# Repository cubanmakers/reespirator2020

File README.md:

# Reespirator 2020

Este repositorio pretende documentar y organizar los pasos para fabricar prototipos de  **Reespirator-2020**, un respirador open-source basado en el sistema de ventilación mecánica Jackson-Rees, diseñado y mejorado a partir de los prototipos elaborados por el equipo de Reesistencia Team para todas aquellas personas, organizaciones o empresas que quieran fabricarlo en cualquier parte del mundo.  

> ESTA DOCUMENTACIÓN ESTÁ EN ELABORACIÓN, COMPRUEBE REGULARMENTE LOS CAMBIOS, LAS PRIMERAS VERSIONES PUBLICADAS ESTÁN DESACTUALIZADAS. 

## Disclaimer
*Recuerde que un respirador es un dispositivo médico que sólo puede ser utilizado por personal cualificado y que un mal respirador o un respirador mal utilizado puede matar.*

La presente documentación **NO PERMITE CONSTRUIR UN RESPIRADOR FINAL**, sólo se publica para que se pueda fabricar PROTOTIPOS para investigación. 

## Info
*¿Qué es Reespirator 2020?*

El dispositivo Reespirator 2020 es un prototipo de sistema respirador de emergencia con elementos disponibles por la mayoría de las personas en cualquier parte del mundo, de rápida construcción y con la capacidad para mantener constantes ventilatorias aceptables en un paciente afecto de [Síndrome de Distrés Respiratorio Agudo](https://es.wikipedia.org/wiki/S%C3%ADndrome_de_dificultad_respiratoria_aguda) o SDRA.

Aunque el origen de Reespirator es España, debido a las regulaciones y validaciones necesarias para los productos médicos, y aunque Reespirator 23 de Reesistencia Team en el que se ha basado este nuevo diseño, ha superado varias pruebas preclínicas con animales, y de compatibilidad electromagnética, suponemos que este dispositivo nunca se llegará a fabricar masivamente en España, dónde afortunadamente lo peor de la crisis del COVID-19 parece que ya ha pasado (08/04/20); esperamos que este y otros diseños puedan ser útiles en otros países.

Aún así no nos damos por vencidos y seguiremos desarrollando el proyecto al menos en 2 versiones:

* Versión low cost (basada en Arduino y con caja de metacrilato, madera...)
* Versión pro (con un autómata PLC + un HMI y caja de chapa plegada en acero inoxidable)

## Primeros pasos
Antes de montar un respirador lea toda la documentación posible e infórmese bien, si necesitas alguna aclaración abra un Issue y lo corregiremos en cuanto podamos. Si crees que puedes mejorar el diseño o el código envíanos un Pull request.

## [Estructura básica](https://gitlab.com/reespirator/reespirator-doc/-/blob/master/CASE.md)
Reespirator 2020 consta de una [caja](https://gitlab.com/reespirator/reespirator-doc/-/blob/master/CASE.md) diseñada para fabricarse mediante corte láser que contiene casi todos elementos del respirador en su interior. En el prototipo actual las piezas del prototipo se han diseñado para su corte por láser en metacrilato si bien la imagen anterior corresponde a la nueva evolución que podrá fabricarse también con chapa plegada.

## [Sistema neumático](https://gitlab.com/reespirator/reespirator-doc/-/blob/master/NEUMATIC.md)
El [sistema neumático](https://gitlab.com/reespirator/reespirator-doc/-/blob/master/NEUMATIC.md) del Reespirator 2020 está basado en un sistema Jackson-Rees. Reespirator 2020 utiliza además una serie de válvulas, sensores de presión y caudal y tubuladuras para hacer llegar al aire a los pulmones del paciente.

## [Mecánica](https://gitlab.com/reespirator/reespirator-doc/-/blob/master/MECHANIC.md)
El [sistema mecánico](https://gitlab.com/reespirator/reespirator-doc/-/blob/master/MECHANIC.md) pretende realizar los movimientos necesarios para realizar las maniobras de inspiración y espiración forzada del paciente mediante elementos mecánicos sustituyendo al personal humano que utilizaría el sistema de ventilación.

## [Electrónica](https://gitlab.com/reespirator/reespirator-doc/-/blob/master/ELECTRONICS.md)
La [electrónica](https://gitlab.com/reespirator/reespirator-doc/-/blob/master/ELECTRONICS.md) de control gestiona el movimiento del motor y los sensores que permiten realizar un control de lazo cerrado automatizado del sistema.
Además de la electrónica de control se emplea una electrónica adicional como interfaz de usuario que permite monitorizar diferentes señales del respirador y modificar en tiempo real diferentes configuraciones del mismo.

## [Firmware](https://gitlab.com/reespirator/reespirator-doc/-/blob/master/FIRMWARE.md)
El sistema de control necesita ser programado con un [firmware](https://gitlab.com/reespirator/reespirator-doc/-/blob/master/FIRMWARE.md) que permita hacer funcionar el dispositivo. Dicho programa se ha realizado conforme a las especificaciones de los especialistas médicos para realizar las funciones para las que el dispositivo fue diseñado.

## [Manual de usuario](https://gitlab.com/reespirator/reespirator-doc/-/blob/master/MANUAL.md)
El dispositivo Reespirator 2020 es un dispositivo médico y su uso sólo debe realizarse por personal especializado. Ofrecemos aquí un breve [manual de uso](https://gitlab.com/reespirator/reespirator-doc/-/blob/master/MANUAL.md) del mismo; pero es el personal sanitario el que sabe los parámetros que deben utilizarse para el tratamiento del paciente.

## Historia y principales cambios de esta versión

El proyecto Reespirator2020 toma como punto de partida el proyecto Reespirator 23 (o 24) v3 de **Reesistencia Team** a partir del cual realizamos un fork.

En esta nueva versión se incluyen principalmente los siguientes cambios:

 - Revisión y reestructuración en profundidad del códido de Arduino para asegurar la robustez de funcionamiento en todos los supuestos.
 - La recuperación del interfaz básico con LCD de 20x04 y elementos sencillos de control (4 pulsadores y un encoder con pulsador).
 - Establecimiento y documentación de una interfaz de comunicación serie que permite la utilización de sistemas (en adelante llamados Display+) de visualización, control y conectividad, que pueden ser utilizados como accesorios para aportar mejor usabilidad al sistema.
 - Se trabaja para estandarizar y popularizar los sensores y electro-válvulas para utilizar partes (comerciales o diseñadas) posibles de conseguir con la situación de emergencia actual y a precios accesibles.

## Repositorio temporal de trabajo para el código de Reespirator2020

El siguiente repositorio se está utilizando como fork de trabajo para transformar el código de Respirator 23 (o 24) v3 de Reesistencia Team (cuyo código se denominó 'batalla') en el código estable que se usará en Respirator 2020 de arduino, cuyo código se denominó  ['retaguardia'](https://gitlab.com/reespirator-arduino).

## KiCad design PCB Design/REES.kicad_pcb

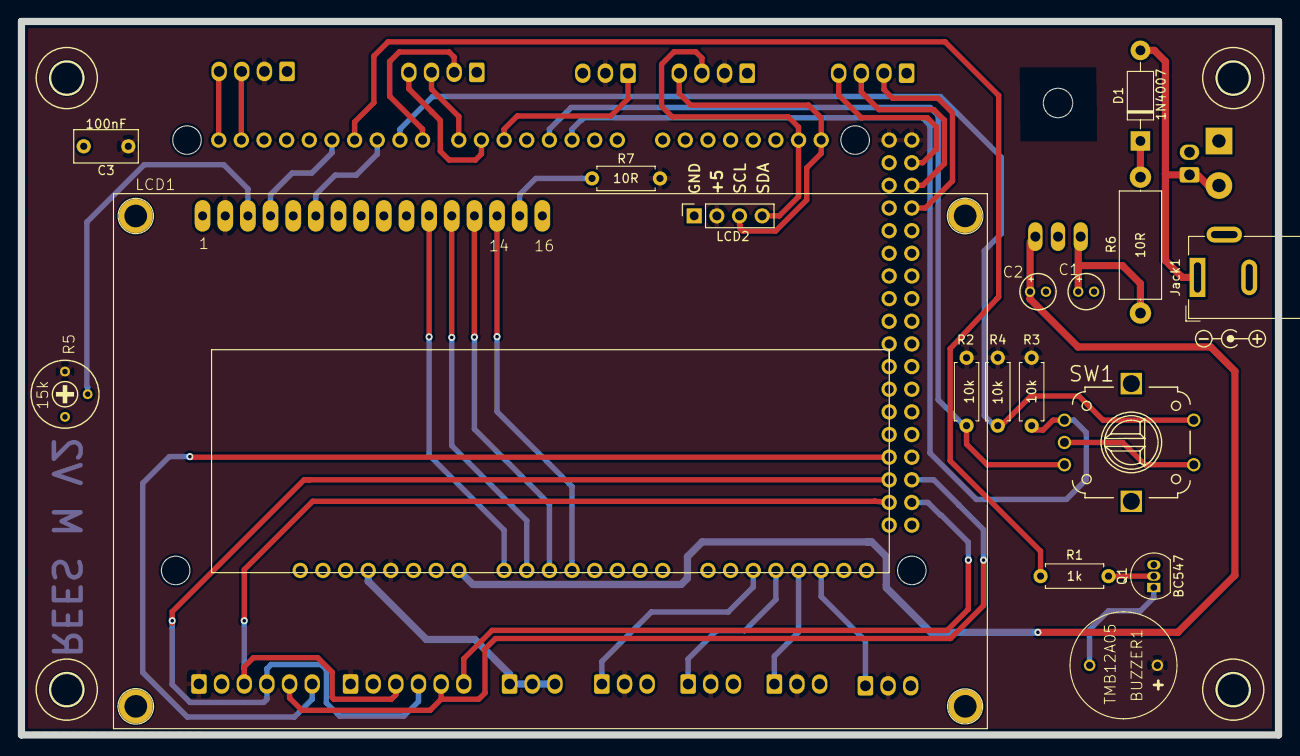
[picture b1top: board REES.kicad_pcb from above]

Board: 2 copper layers, 141.0 x 80.0 mm, 37 parts (0 on the bottom side), 41 nets.

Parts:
3V3: Conn_3V3; Molex_KK-254_AE-6410-03A_1x03_P2.54mm_Vertical
Arduino1: Arduino_Mega2560_Shield
BUZZER1: TMB12A05
C1: 330n; E1,8-4
C2: 100n; E1,8-4
C3: 100nF; C_Rect_L7.0mm_W3.5mm_P5.00mm
D1: 1N4007; D_DO-41_SOD81_P10.16mm_Horizontal
DRIVER0, DRIVER1: 22-?-0405-7048; Molex_KK-254_AE-6410-04A_1x04_P2.54mm_Vertical
H1, H2, H3, H4: HOLES_MOUNT-HOLE3.6; HOLES_3,6
HALL1: 22-?-0305-7038; Molex_KK-254_AE-6410-03A_1x03_P2.54mm_Vertical
I2C0, I2C1: 22-?-0405-7048; Molex_KK-254_AE-6410-04A_1x04_P2.54mm_Vertical
J1: Screw_Terminal_01x02; Altech_AK300_1x02_P5.00mm_45-Degree
Jack1: Jack-DC; BarrelJack_Wuerth_6941xx301002
LCD1: L2034-T
LCD2: Conn_I2C_OLED; PinSocket_1x04_P2.54mm_Vertical
Q1: BC547; TO-92_Inline
R1: 1k; R_Axial_DIN0207_L6.3mm_D2.5mm_P7.62mm_Horizontal
R2, R3, R4: 10k; R_Axial_DIN0207_L6.3mm_D2.5mm_P7.62mm_Horizontal
R5: 15k; RTRIM3339P
R6: 10R; R_Axial_DIN0414_L11.9mm_D4.5mm_P15.24mm_Horizontal
R7: 10R; R_Axial_DIN0207_L6.3mm_D2.5mm_P7.62mm_Horizontal
REGULADOR1: LINEAR_7812T; LINEAR_TO220H
SENS0: Conn_Analog0; Molex_KK-254_AE-6410-03A_1x03_P2.54mm_Vertical
SENS1: Conn_Analog1; Molex_KK-254_AE-6410-03A_1x03_P2.54mm_Vertical
SENS2: Conn_Analog2; Molex_KK-254_AE-6410-03A_1x03_P2.54mm_Vertical
SENS3: Conn_Analog3; Molex_KK-254_AE-6410-03A_1x03_P2.54mm_Vertical
SPI0: Conn_SPI0; Molex_KK-254_AE-6410-06A_1x06_P2.54mm_Vertical
SPI1: Conn_SPI1; Molex_KK-254_AE-6410-06A_1x06_P2.54mm_Vertical
SW1: ENCODER_SW1-PEC12; PEC12_INCREMENTAL_ENCODER
VIN1: 22-?-0205-7028; Molex_KK-254_AE-6410-02A_1x02_P2.54mm_Vertical

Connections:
+5V: Arduino1.5V1, Arduino1.5V3, Arduino1.5V4, BUZZER1.1, C3.1, HALL1.2, I2C0.2, I2C1.2, LCD1.2, LCD2.2, R2.2, R3.2, R4.2, R5.3, R7.2, SENS0.2, SENS1.2, SENS2.2, SENS3.2, SPI0.1, SPI1.1
+12V: Arduino1.VIN, C2.+, REGULADOR1.3
+24V: C1.+, R6.2, REGULADOR1.1
/3V3: 3V3.1, 3V3.2, 3V3.3, Arduino1.3V3
/BUZZ: Arduino1.D11, R1.1
/CLK: Arduino1.D2, R3.1, SW1.A
/D4: Arduino1.A0, LCD1.11
/D5: Arduino1.A1, LCD1.12
/D6: Arduino1.A2, LCD1.13
/D7: Arduino1.A3, LCD1.14
/DIR0: Arduino1.D7, DRIVER0.3
/DIR1: Arduino1.D25, DRIVER1.3
/DT: Arduino1.D3, R2.1, SW1.B
/E: Arduino1.D10, LCD1.6
/ENA0: Arduino1.D8, DRIVER0.2
/ENA1: Arduino1.D27, DRIVER1.2
/HALL: Arduino1.D5, HALL1.1
/MISO: Arduino1.D50, SPI0.4, SPI1.4
/MOSI: Arduino1.D51, SPI0.5, SPI1.5
/PUL0: Arduino1.D6, DRIVER0.4
/PUL1: Arduino1.D23, DRIVER1.4
/RS: Arduino1.D12, LCD1.4
/SCK: Arduino1.D52, SPI0.3, SPI1.3
/SCL1: Arduino1.D21, I2C0.4, LCD2.3
/SCL2: Arduino1.SCL, I2C1.4
/SDA1: Arduino1.D20, I2C0.3, LCD2.4
/SDA2: Arduino1.SDA, I2C1.3
/SENS0: Arduino1.A10, SENS0.1
/SENS1: Arduino1.A11, SENS1.1
/SENS2: Arduino1.A12, SENS2.1
/SENS3: Arduino1.A13, SENS3.1
/SS0: Arduino1.D53, SPI0.6
/SS1: Arduino1.D48, SPI1.6
/SW: Arduino1.D9, R4.1, SW1.P1
GND: Arduino1.GND1, Arduino1.GND2, Arduino1.GND3, Arduino1.GND5, Arduino1.GND6, C1.-, C2.-, C3.2, DRIVER0.1, DRIVER1.1, HALL1.3, I2C0.1, I2C1.1, J1.1, Jack1.2, LCD1.1, LCD1.5, LCD1.16, LCD2.1, Q1.3, R5.1, REGULADOR1.2, SENS0.3, SENS1.3, SENS2.3, SENS3.3, SPI0.2, SPI1.2, SW1.C, SW1.P2, VIN1.2
unnamed: BUZZER1.2, Q1.1
unnamed: D1.1, R6.1
unnamed: D1.2, J1.2, Jack1.1, VIN1.1
unnamed: LCD1.3, R5.2
unnamed: LCD1.15, R7.1
unnamed: Q1.2, R1.2

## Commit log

2020-03-19 Documentación desde el repositorio de software
2020-03-19 reorganizando contenido de carpetas
2020-03-19 migrando archivos desde el repo soft
2020-03-21 Actualizada PCB y esquemático. Se ha cambiado un transistor y retocado alguna pista (por Antonio Ruiz)
2020-03-23 Actualizada PCB y Esquematico por Antonio Ruiz (@antoniorn1). Actualizada Documentación por Iván Torres (@itorres1). Actualizado BOM por Joaquín Cubillo
2020-03-23 Actualizado readme
2020-03-23 Añadido equipo de desarolladores
2020-03-23 Cambios menores
2020-03-23 Team credits
2020-03-23 Fabrication files added
2020-03-23 Actualizado BOM y créditos
2020-03-24 PCB Silkscreen modified
2020-04-03 Update enlace codigo.txt, Documentacion Reespirator23.pdf, Reespirator23v4.x_t files
2020-04-03 Simplify readme
2020-04-04 Update readme and clean deprecated content
2020-04-04 Fix readme anchor
2020-04-04 hardware requirements
2020-04-05 Actualización Readme.md
2020-04-05 Creación de los documentos de cada sección
2020-04-05 Añadido manual de uso
2020-04-05 actualización disclaimer
2020-04-05 Updating electronics assembly
2020-04-05 Clean assembly repo
    Clean duplicated info from assembly repository
2020-04-05 Electronic.md update
2020-04-05 Disclaimer update
2020-04-05 Firm update
2020-04-06 assembly file
2020-04-06 Add new images directory
2020-04-06 Upload New File
2020-04-06 Add new file
2020-04-06 Change name to MECHANIC.md
2020-04-06 Reespirator image added to README.md
2020-04-07 Moving images to correct directory
2020-04-07 Fix image links
2020-04-07 Update several docs
2020-04-08 update contents
2020-04-08 Update README.md
    Fork
2020-04-09 Actualización del disclaimer y advertencias
2020-04-09 Add LICENSE
2020-04-09 Add HMI images
2020-04-09 Deleted old files
2020-04-10 Redesign
2020-04-10 Corrijo link
2020-04-10 Updated PLC-ELECTRONICS.md
2020-04-10 Update PLC-ELECTRONICS with images.
2020-04-10 Cambio URL imagenes
2020-04-10 Minor changes on PLC-ELECTRONICS.md
2020-04-10 Chapas
2020-04-10 Fix links
2020-04-10 Electronics versions
2020-04-10 Enlaces a las diferentes electrónicas
2020-04-10 Arduino y PLC
2020-04-10 cases
2020-04-10 fix photos
2020-04-10 Nema24
2020-04-10 caudalímetro
2020-04-10 Update LICENSE
2020-04-10 update PLC ver
2020-04-10 neumatic update
2020-04-10 PLC firm update info
2020-04-10 Update PLC info
2020-04-10 Add new directory
2020-04-10 update electronics arduino
2020-04-10 rename stl file
2020-04-10 Upload chapa files
2020-04-10 Update Reespirator2020 PLC v1 - SIEMENS Simatic S7-1200 CPU 1512/README.md, Reespirator2020 ARD v1 - Arduino Mega 2560/README.md, Display+ BB-SW v1 - BeagleBone with ShareWave/README.md, Display+ Lap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
2020-04-10 move design files
2020-04-10 Update case lock images
2020-04-10 Update comments
2020-04-10 fix image link
2020-04-10 fix dir
2020-04-10 Case file fix
2020-04-10 Actualizado el archivo de la carcasa superior
2020-04-10 Update README.md file
2020-04-10 cuna
2020-04-10 update files
2020-04-10 STL file links
2020-04-10 update stl files
2020-04-10 add stl files
2020-04-10 documentación
2020-04-10 Add CHANGELOG
2020-04-10 Add CONTRIBUTING
2020-04-11 Update manual style
2020-04-11 arduino reespirator23 firm
2020-04-11 organizando info del firm y los hmi
2020-04-11 Montaje de metacrilato (versión previa sin terminar)
2020-04-11 Update BB
2020-04-12 Update ARDUINO-ELECTRONICS.md, interfaz_arduino_hm.png, images/interfaz_arduino_hm.png files
